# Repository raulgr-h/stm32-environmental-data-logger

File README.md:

# STM32L431 Environmental Data Logger

A custom embedded environmental data logger built around the STM32L431 microcontroller.

The project began as a hand-assembled Rev A PCB integrating an SHT41 environmental sensor, SPI microSD storage, RTC timestamping, and STM32 firmware. Rev A was brought through board bring-up, firmware integration, protocol debugging, long-duration logging, and electrical characterization.

Development has now progressed to a Rev B redesign informed by measured Rev A behavior, with emphasis on lower-power operation, improved nonvolatile storage, BLE connectivity, and systematic hardware validation.

---

## Project Status

### Rev A — Functional and Characterized

The core Rev A environmental logging path has been successfully brought up and verified.

Verified functionality includes:

- STM32L431 firmware execution and SWD debugging
- SHT41 temperature and relative-humidity measurements over I2C
- SPI-mode microSD initialization and sector access
- FatFs mount, file open, append, write, sync, and close operations
- STM32 RTC initialization and timestamp generation
- RTC-timestamped, PC-readable CSV logging
- Nonblocking push-button-controlled logging
- Multi-hour logging operation
- Zero observed SPI transfer failures during verified long-duration runs
- Logic-analyzer verification of I2C and SPI transactions
- Oscilloscope and Analog Discovery 2 electrical measurements
- Board-level current and supply-transient characterization
- Automated CR2032 pulse-load characterization

Rev A is retained as the verified hardware baseline for continued development.

### Rev B — In Development

Rev B is being developed from Rev A test results and system-level lessons.

Current design changes include:

- Replacement of microSD storage with an ST M95P16 SPI Page EEPROM
- Addition of a 32.768 kHz LSE crystal for RTC and low-power operation
- Addition of a CYBLE-416045-02 BLE module
- STM32-to-BLE UART communication
- Dedicated BLE programming/debug access
- Revised low-power architecture
- Updated user controls and interfaces
- PCB changes informed by measured battery and transient-load behavior

Rev B schematic development is maintained separately from the archived Rev A hardware baseline.

---

## System Architecture

### Rev A

- **Microcontroller:** STM32L431CBT6
- **Environmental Sensor:** Sensirion SHT41
- **Sensor Interface:** I2C
- **Storage:** microSD over SPI
- **Filesystem:** FatFs
- **Timekeeping:** STM32 RTC
- **Firmware:** Embedded C using STM32 HAL
- **PCB Design:** KiCad
- **Development Environment:** STM32CubeIDE
- **Test Equipment:** Digilent Analog Discovery 2, DMM, oscilloscope, and logic analyzer

### Rev B

- **Microcontroller:** STM32L431CBT6
- **Environmental Sensor:** Sensirion SHT41
- **Nonvolatile Storage:** ST M95P16 SPI Page EEPROM
- **Wireless Interface:** Infineon CYBLE-416045-02 BLE module
- **BLE Host Interface:** UART
- **RTC Reference:** External 32.768 kHz LSE crystal
- **PCB Design:** KiCad

---

## Firmware Development

Rev A firmware includes:

- STM32 HAL peripheral configuration
- SHT41 command and measurement handling
- Low-level SPI SD communication
- SD initialization using CMD0, CMD8, CMD55, ACMD41, and CMD58
- Sector-level SD access
- FatFs disk-I/O integration
- RTC initialization and timestamp generation
- Backup-register handling for RTC state
- Timestamped CSV creation and append operations
- Nonblocking push-button debounce and logging-state control
- Reusable sensor-to-storage logging routines
- SPI error instrumentation
- Time-based communication timeout handling

Rev B firmware development will extend the platform with:

- SPI EEPROM storage
- Lower-power operating modes
- BLE coprocessor communication
- Wireless environmental-data transfer

---

## Automated Test and Characterization

A Python-based automated test environment was developed using the Digilent WaveForms SDK and Analog Discovery 2.

The test fixture uses transistor-switched resistive loads and synchronized analog acquisition to characterize battery and PCB supply behavior under controlled transient loads.

Capabilities include:

- Automated selection of multiple load conditions
- Configurable pulse durations
- Repeated transient tests
- Analog acquisition at up to 100 kS/s
- Synchronized battery and shunt-voltage measurement
- Current calculation from calibrated shunt measurements
- Pre-pulse baseline measurement
- Minimum battery-voltage detection
- PCB supply-voltage analysis
- Voltage-droop calculation
- Recovery-voltage analysis
- Pulse-duration validation
- Acquisition-integrity monitoring
- Per-test raw waveform CSV logging
- Reduced summary-metric generation
- Automatic load removal after each test
- Configurable 2.40 V low-voltage safety cutoff

The characterization framework progressed from basic manual load switching and averaged measurements to automated transient waveform capture, focused pulse testing, and repeatability testing.

These measurements are being used to inform Rev B power, storage, and low-power design decisions.

---

## Electrical Characterization

Rev A current and supply behavior were measured during normal environmental logging and controlled load testing.

Verified observations include:

- Approximately **2.1 mA average board current** during 5 s interval logging
- Sampled transient current peaks of approximately **25 mA** at 500 kHz during sensor and microSD activity
- Measurable VDD droop correlated with current transients
- Successful CSV writes despite the observed transient supply behavior
- Repeatable CR2032 transient-load measurements using automated acquisition
- Preservation of raw waveforms for later engineering analysis

The automated test setup enables battery behavior to be compared across different loads, pulse durations, and repeated test runs rather than relying only on static current measurements.

---

## Verification

The system has been verified using:

- STM32CubeIDE debugging
- Runtime firmware instrumentation
- DMM resistance, continuity, and voltage measurements
- Oscilloscope measurements
- Digilent Analog Discovery 2 analog acquisition
- Logic-analyzer protocol captures
- Long-duration CSV logging
- Automated transient-load testing
- Repeatability testing
- Git revision and diff analysis during debugging

Key verified results include:

- `FR_OK` for successful FatFs mount, open, write, sync, and close operations
- `HAL_OK` during verified SHT41 communication
- Successful SPI SD initialization
- Successful CMD17 read transactions
- Verified SHT41 I2C command and response transactions
- RTC-timestamped, PC-readable CSV files
- Button input correlated with subsequent sensor sampling and storage activity
- Multi-hour logging with zero observed SPI transfer failures during verified runs

---

## Debugging Case Studies

### SD Hardware Fault

During Rev A bring-up, the SD card ground connection measured approximately 5 MΩ because of a poor solder joint.

The fault was isolated using resistance and continuity measurements and corrected by reflowing the affected connection.

This restored a valid low-resistance ground connection and allowed SD communication debugging to continue.

### FatFs Write Failure

A later firmware issue caused the first FatFs write operation to appear to hang.

Investigation showed that the SPI peripheral remained at the low initialization clock after SD startup while the disk driver used iteration-count-based ready timeouts.

The corrective actions included:

- Increasing the SPI clock after SD initialization
- Replacing iteration-count polling with `HAL_GetTick()`-based timeouts
- Adding SPI transfer-failure instrumentation

After correction, file open, write, sync, and close operations completed successfully.

### CubeMX Regeneration Regression

A later STM32CubeMX regeneration overwrote the customized `user_diskio.c` implementation, causing FatFs operations to return `FR_NOT_READY`.

The regression was isolated using:

- Runtime return-code instrumentation
- Git revision comparison
- Source diff analysis

Restoring the previously verified disk-I/O implementation recovered normal SD and FatFs operation.

This demonstrated the use of source control not only for version management, but also as a firmware-debugging and regression-analysis tool.

---

## Hardware Revision Strategy

Rev A is retained as a frozen hardware baseline rather than being modified in place.

Rev B development is maintained separately so design changes can be traced back to measured Rev A behavior and validation results.

```text
hardware/kicad/
├── rev-a/          Verified Rev A hardware baseline
├── rev-b/          Rev B hardware development
├── symbols/        Project-specific schematic symbols
├── footprints/     Project-specific PCB footprints
└── 3dmodels/       Component mechanical models
```

The `rev-a-hardware` Git tag preserves the Rev A hardware milestone.

---

## Repository Structure

```text
hardware/
└── kicad/
    ├── rev-a/
    ├── rev-b/
    ├── symbols/
    ├── footprints/
    └── 3dmodels/

firmware/
└── STM32CubeIDE project and embedded firmware

test/
├── scripts/
│   └── ate/
├── raw-data/
├── processed-data/
└── results/

docs/
├── design/
├── bringup/
└── images/

releases/
└── Release and milestone documentation
```

### Automated Test Scripts

The primary automated characterization scripts are maintained under:

```text
test/scripts/ate/
```

They cover:

- Full pulse-load characterization
- Focused pulse testing
- Repeatability testing
- Rev A system-level load testing

Raw acquisition data and processed engineering results are maintained separately to preserve traceability between measurement evidence and reduced summary metrics.

---

## Engineering Scope

This project serves as an end-to-end embedded hardware development platform covering:

- PCB schematic and layout development
- Hardware revision control
- Hand assembly and board bring-up
- STM32 embedded firmware development
- I2C and SPI protocol implementation
- Sensor integration
- Embedded filesystem integration
- RTC and timestamped data acquisition
- Hardware/firmware debugging
- Oscilloscope and logic-analyzer validation
- Automated hardware testing
- Python test automation
- Battery and transient-load characterization
- Root-cause failure analysis
- Design-for-low-power development
- BLE subsystem development
- Git/GitHub engineering workflow

---

## Next Development Steps

Current development is focused on Rev B, including:

- Completing Rev B schematic design review
- PCB layout and design-rule verification
- M95P16 storage-driver development
- BLE subsystem prototyping and UART communication
- Low-power firmware development
- Rev B assembly and bring-up
- Power-consumption comparison between Rev A and Rev B
- Environmental logging validation using the revised architecture

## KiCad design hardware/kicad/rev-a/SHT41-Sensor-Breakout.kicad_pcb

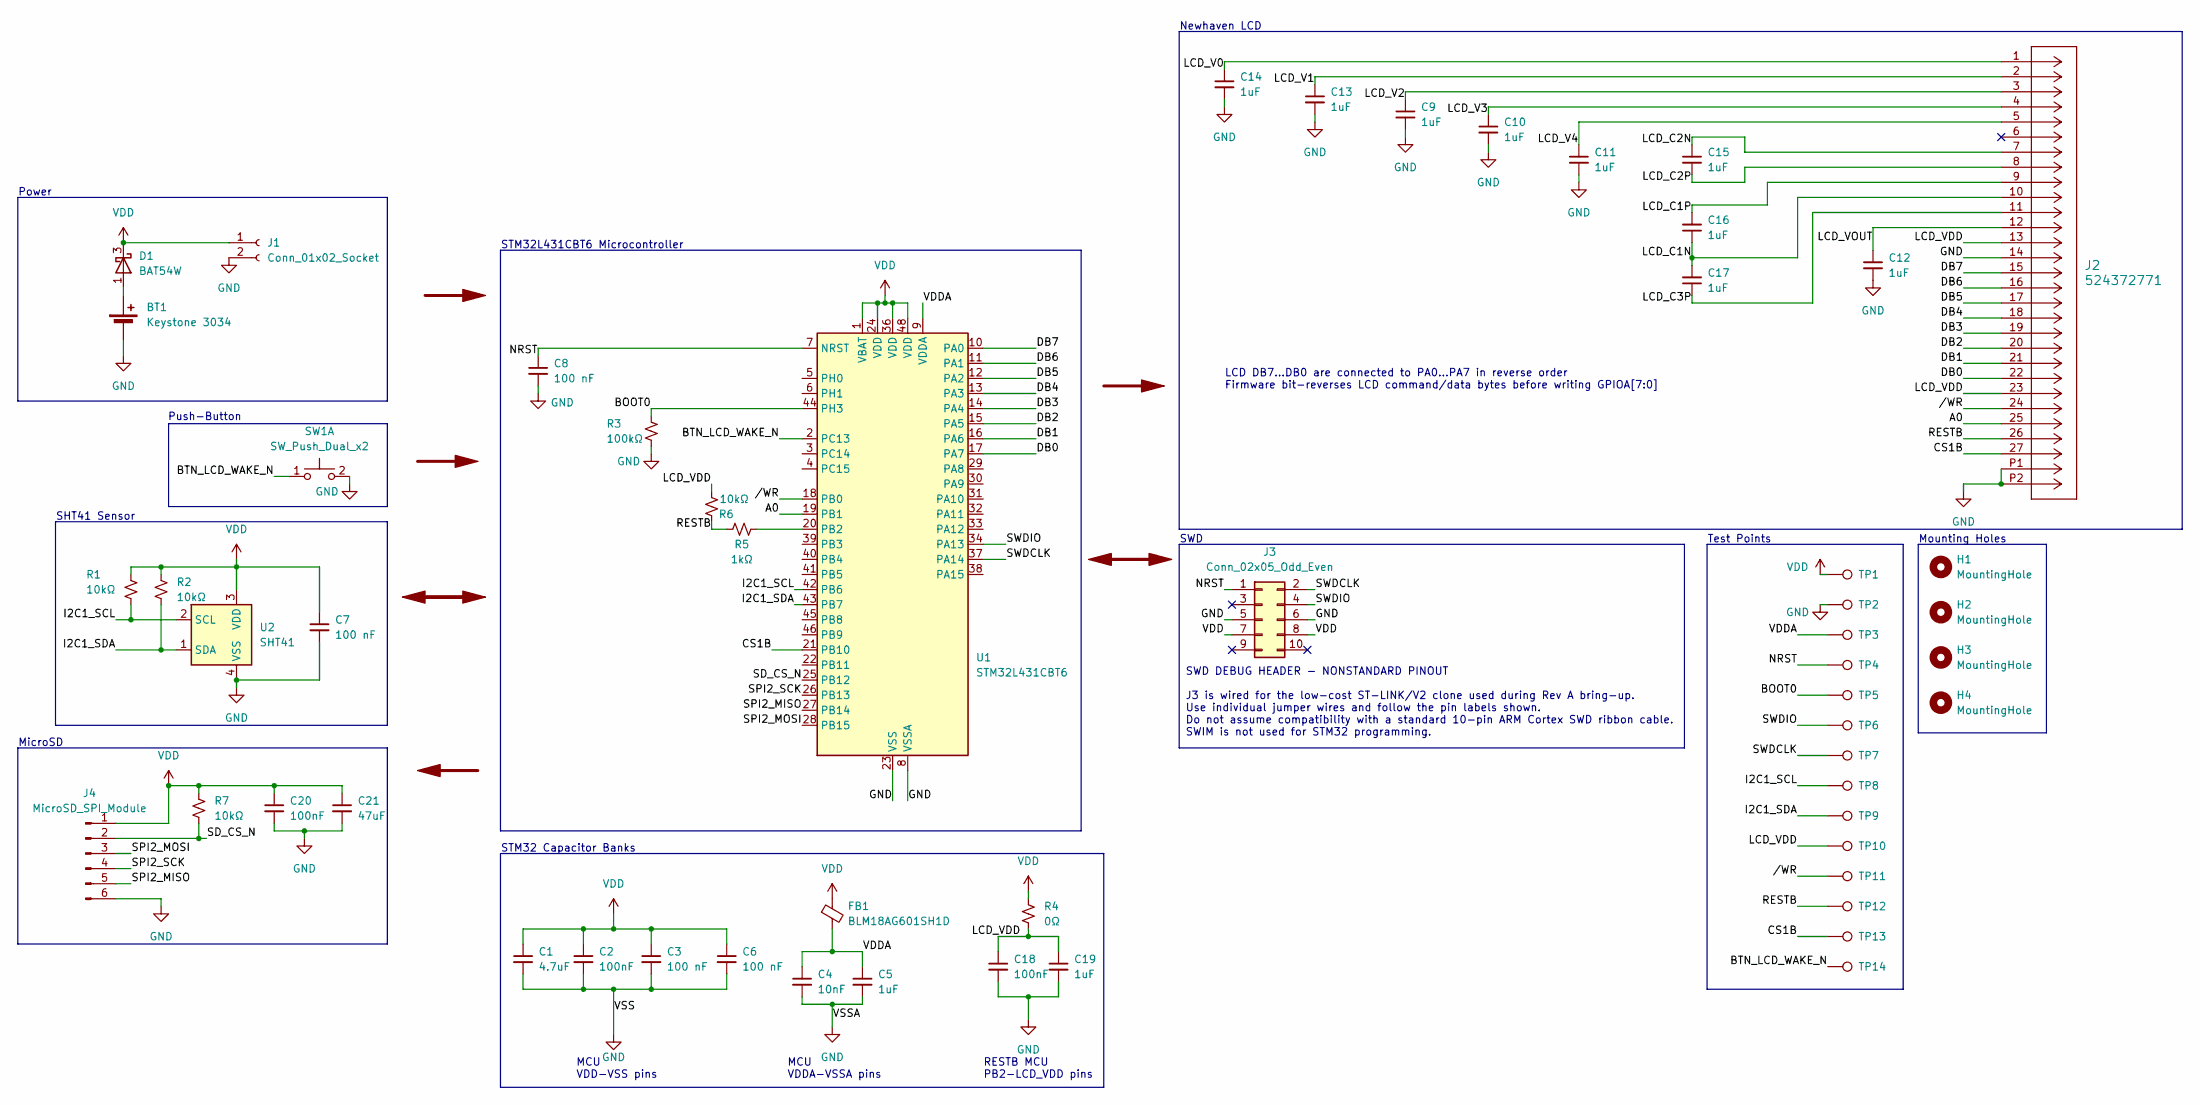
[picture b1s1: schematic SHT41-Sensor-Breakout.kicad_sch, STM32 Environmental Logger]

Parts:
BT1: Keystone 3034; BatteryHolder_Keystone_3034_1x20mm
C1: 4.7uF; C_0805_2012Metric
C2, C18, C20: 100nF; C_0805_2012Metric
C3, C6, C7, C8: 100 nF; C_0805_2012Metric
C4: 10nF; C_0805_2012Metric
C5, C9, C10, C11, C12, C13, C14, C15, C16, C17, C19: 1uF; C_0805_2012Metric
C21: 47uF; C_0805_2012Metric
D1: BAT54W; SOT-323_SC-70
FB1: BLM18AG601SH1D; L_0805_2012Metric
H1, H2, H3, H4: MountingHole; MountingHole_3.2mm_M3
J1: Conn_01x02_Socket; PinHeader_1x02_P2.54mm_Vertical
J2: 524372771; Molex_52437-2771_Custom
J3: Conn_02x05_Odd_Even; PinHeader_2x05_P2.54mm_Vertical
J4: MicroSD_SPI_Module; PinHeader_1x06_P2.54mm_Vertical
R1, R2, R6, R7: 10kΩ; R_0805_2012Metric
R3: 100kΩ; R_0805_2012Metric
R4: 0Ω; R_0805_2012Metric
R5: 1kΩ; R_0805_2012Metric
SW1: SW_Push_Dual_x2; SW_Push_1P1T_NO_E-Switch_TL3301NxxxxxG
TP1: VDD; TestPoint_Pad_D1.5mm
TP2: GND; TestPoint_Pad_D1.5mm
TP3: VDDA; TestPoint_Pad_D1.5mm
TP4: NRST; TestPoint_Pad_D1.5mm
TP5: BOOT0; TestPoint_Pad_D1.5mm
TP6: SWDIO; TestPoint_Pad_D1.5mm
TP7: SWDCLK; TestPoint_Pad_D1.5mm
TP8: SCL; TestPoint_Pad_D1.5mm
TP9: SDA; TestPoint_Pad_D1.5mm
TP10: LCD_VDD; TestPoint_Pad_D1.5mm
TP11: WR; TestPoint_Pad_D1.5mm
TP12: RESTB; TestPoint_Pad_D1.5mm
TP13: CS1B; TestPoint_Pad_D1.5mm
TP14: BTN; TestPoint_Pad_D1.5mm
U1: STM32L431CBT6; LQFP-48_7x7mm_P0.5mm
U2: SHT41; Sensirion_DFN-4_1.5x1.5mm_P0.8mm_SHT4x_NoCentralPad

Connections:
/A0: J2.25, U1.19 (PB1)
/BOOT0: R3.1, TP5.1 (1_1), U1.44 (PH3)
/BTN_LCD_WAKE_N: SW1.1 (C), TP14.1 (1_1), U1.2 (PC13)
/CS1B: J2.27, TP13.1 (1_1), U1.21 (PB10)
/DB0: J2.22, U1.17 (PA7)
/DB1: J2.21, U1.16 (PA6)
/DB2: J2.20, U1.15 (PA5)
/DB3: J2.19, U1.14 (PA4)
/DB4: J2.18, U1.13 (PA3)
/DB5: J2.17, U1.12 (PA2)
/DB6: J2.16, U1.11 (PA1)
/DB7: J2.15, U1.10 (PA0)
/I2C1_SCL: R1.2, TP8.1 (1_1), U1.42 (PB6), U2.2 (SCL)
/I2C1_SDA: R2.2, TP9.1 (1_1), U1.43 (PB7), U2.1 (SDA)
/LCD_C1N: C16.1, C17.2, J2.10
/LCD_C1P: C16.2, J2.9
/LCD_C2N: C15.1, J2.7
/LCD_C2P: C15.2, J2.8
/LCD_C3P: C17.1, J2.11
/LCD_V0: C14.1, J2.1
/LCD_V1: C13.1, J2.2
/LCD_V2: C9.1, J2.3
/LCD_V3: C10.1, J2.4
/LCD_V4: C11.1, J2.5
/LCD_VDD: C18.1, C19.1, J2.13, J2.23, R4.2, R6.2, TP10.1 (1_1)
/LCD_VOUT: C12.1, J2.12
/NRST: C8.1, J3.1, TP4.1 (1_1), U1.7 (NRST)
/RESTB: J2.26, R5.2, R6.1, TP12.1 (1_1)
/SD_CS_N: J4.2, R7.2, U1.25 (PB12)
/SPI2_MISO: J4.5, U1.27 (PB14)
/SPI2_MOSI: J4.3, U1.28 (PB15)
/SPI2_SCK: J4.4, U1.26 (PB13)
/SWDCLK: J3.2, TP7.1 (1_1), U1.37 (PA14)
/SWDIO: J3.4, TP6.1 (1_1), U1.34 (PA13)
/VDDA: C4.1, C5.1, FB1.2, TP3.1 (1_1), U1.9 (VDDA)
//WR: J2.24, TP11.1 (1_1), U1.18 (PB0)
GND: BT1.2 (-), C1.2, C2.2, C3.2, C4.2, C5.2, C6.2, C7.2, C8.2, C9.2, C10.2, C11.2, C12.2, C13.2, C14.2, C18.2, C19.2, C20.2, C21.2, J1.2, J2.14, J2.P1, J2.P2, J3.5, J3.6, J4.6, R3.2, SW1.2 (D), TP2.1 (1_1), U1.8 (VSSA), U1.23 (VSS), U1.35 (VSS), U1.47 (VSS), U2.4 (VSS)
unnamed: BT1.1 (+), D1.1 (A)
unnamed: R5.1, U1.20 (PB2)
VDD: C1.1, C2.1, C3.1, C6.1, C7.1, C20.1, C21.1, D1.3 (K), FB1.1, J1.1, J3.7, J3.8, J4.1, R1.1, R2.1, R4.1, R7.1, TP1.1 (1_1), U1.1 (VBAT), U1.24 (VDD), U1.36 (VDD), U1.48 (VDD), U2.3 (VDD)

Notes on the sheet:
SWD DEBUG HEADER - NONSTANDARD PINOUT J3 is wired for the low-cost ST-LINK/V2 clone used during Rev A bring-up. Use individual jumper wires and follow the pin labels shown. Do not assume compatibility with a standard 10-pin ARM Cortex SWD ribbon cable. SWIM is not used for STM32 programming.
SHT41 Sensor
Test Points
MCU VDD-VSS pins
Newhaven LCD
MCU VDDA-VSSA pins
LCD DB7...DB0 are connected to PA0...PA7 in reverse order Firmware bit-reverses LCD command/data bytes before writing GPIOA[7:0]
STM32L431CBT6 Microcontroller
Push-Button
Power
SWD
MicroSD
RESTB MCU PB2-LCD_VDD pins
STM32 Capacitor Banks
Mounting Holes

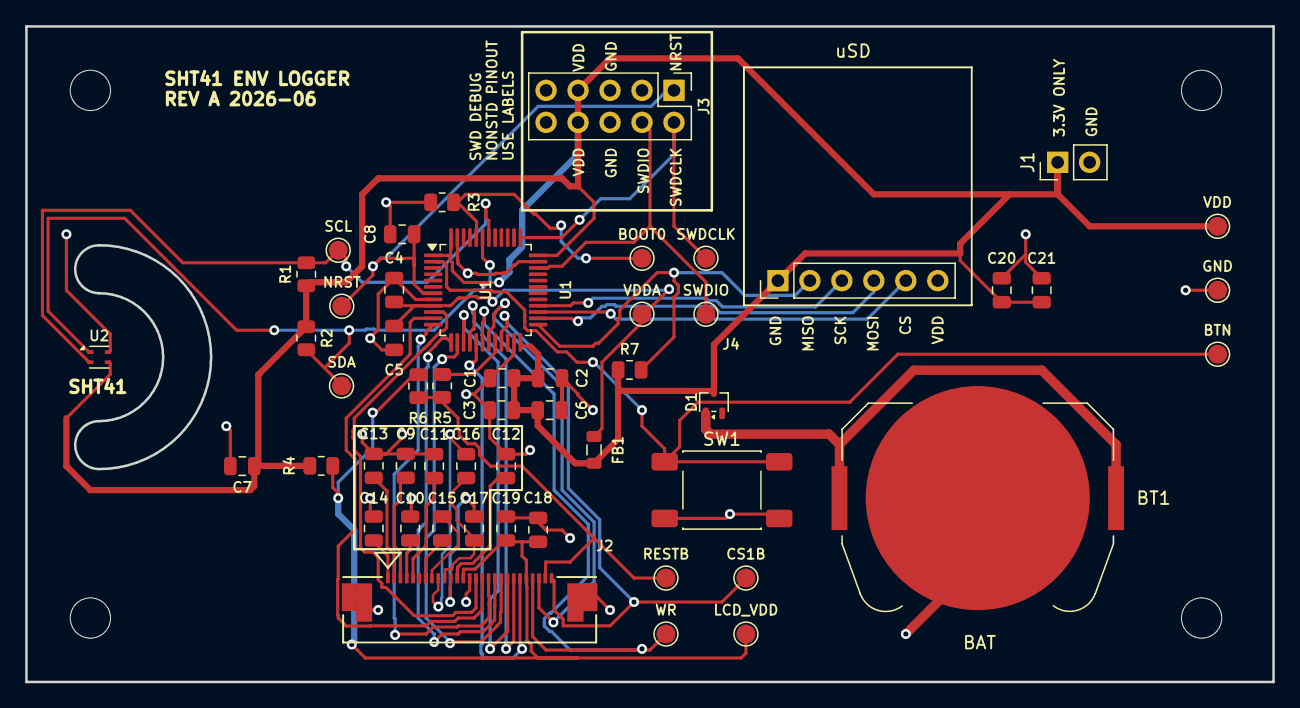
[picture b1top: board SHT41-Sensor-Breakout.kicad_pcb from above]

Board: 2 copper layers, 99.1 x 52.1 mm, 56 parts (0 on the bottom side), 40 nets.

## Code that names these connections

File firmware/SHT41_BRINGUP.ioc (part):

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Mcu.Name=STM32L431C(B-C)Tx
Mcu.Package=LQFP48
Mcu.UserName=STM32L431CBTx
PA0.GPIOParameters=GPIO_Label,GPIO_ModeDefaultOutputPP
PA0.GPIO_Label=LCD_DB7
PA0.GPIO_ModeDefaultOutputPP=GPIO_MODE_OUTPUT_PP
PA0.Signal=GPIO_Output
PA1.GPIOParameters=GPIO_Label
PA1.GPIO_Label=LCD_DB6
PA1.Signal=GPIO_Output
PA10.Signal=GPIO_Analog
PA11.Signal=GPIO_Analog
PA12.Signal=GPIO_Analog
PA13\ (JTMS-SWDIO).Mode=Serial_Wire
PA13\ (JTMS-SWDIO).Signal=SYS_JTMS-SWDIO
PA14\ (JTCK-SWCLK).Mode=Serial_Wire
PA14\ (JTCK-SWCLK).Signal=SYS_JTCK-SWCLK
PA15\ (JTDI).Signal=GPIO_Analog
PA2.GPIOParameters=GPIO_Label
PA2.GPIO_Label=LCD_DB5
PA2.Signal=GPIO_Output
PA3.GPIOParameters=GPIO_Label
PA3.GPIO_Label=LCD_DB4
PA3.Signal=GPIO_Output
PA4.GPIOParameters=GPIO_Label
PA4.GPIO_Label=LCD_DB3
PA4.Signal=GPIO_Output
PA5.GPIOParameters=GPIO_Label
PA5.GPIO_Label=LCD_DB2
PA5.Signal=GPIO_Output
PA6.GPIOParameters=GPIO_Label
PA6.GPIO_Label=LCD_DB1
PA6.Signal=GPIO_Output
PA7.GPIOParameters=GPIO_Label
PA7.GPIO_Label=LCD_DB0
PA7.Signal=GPIO_Output
PA8.Signal=GPIO_Analog
PA9.Signal=GPIO_Analog
PB0.GPIOParameters=PinState,GPIO_Label
PB0.GPIO_Label=LCD_WR_N
PB0.PinState=GPIO_PIN_SET
PB0.Signal=GPIO_Output
PB1.GPIOParameters=GPIO_Label
PB1.GPIO_Label=LCD_A0
PB1.Signal=GPIO_Output
PB10.GPIOParameters=PinState,GPIO_Label
PB10.GPIO_Label=LCD_CS_N
PB10.PinState=GPIO_PIN_SET
PB10.Signal=GPIO_Output
PB11.Signal=GPIO_Analog
PB12.GPIOParameters=PinState,GPIO_PuPd,GPIO_Label
PB12.GPIO_Label=SD_CS_N
PB12.GPIO_PuPd=GPIO_PULLUP
PB12.PinState=GPIO_PIN_SET
PB12.Signal=GPIO_Output
PB13.GPIOParameters=GPIO_Label
PB13.GPIO_Label=SD_SCK
PB13.Mode=Full_Duplex_Master
PB13.Signal=SPI2_SCK
PB14.GPIOParameters=GPIO_PuPd,GPIO_Label
PB14.GPIO_Label=SD_MISO
PB14.GPIO_PuPd=GPIO_PULLUP
PB14.Mode=Full_Duplex_Master
PB14.Signal=SPI2_MISO
PB15.GPIOParameters=GPIO_PuPd,GPIO_Label
PB15.GPIO_Label=SD_MOSI
PB15.GPIO_PuPd=GPIO_PULLUP
PB15.Mode=Full_Duplex_Master
PB15.Signal=SPI2_MOSI
PB2.GPIOParameters=PinState,GPIO_Label
PB2.GPIO_Label=LCD_RESET_N
PB2.PinState=GPIO_PIN_SET
PB2.Signal=GPIO_Output
PB3\ (JTDO-TRACESWO).Signal=GPIO_Analog
PB4\ (NJTRST).Signal=GPIO_Analog
PB5.Signal=GPIO_Analog
PB6.Mode=I2C
PB6.Signal=I2C1_SCL
PB7.Mode=I2C
PB7.Signal=I2C1_SDA
PB8.Signal=GPIO_Analog
PB9.Signal=GPIO_Analog
PC13.GPIOParameters=GPIO_PuPd,GPIO_Label
PC13.GPIO_Label=BTN_LCD_WAKE_N
PC13.GPIO_PuPd=GPIO_PULLUP
PC13.Signal=GPIO_Input
PC14-OSC32_IN\ (PC14).Signal=GPIO_Analog
PC15-OSC32_OUT\ (PC15).Signal=GPIO_Analog
PH0-OSC_IN\ (PH0).Signal=GPIO_Analog
PH1-OSC_OUT\ (PH1).Signal=GPIO_Analog
RCC.HSE_VALUE=8000000
board=custom
